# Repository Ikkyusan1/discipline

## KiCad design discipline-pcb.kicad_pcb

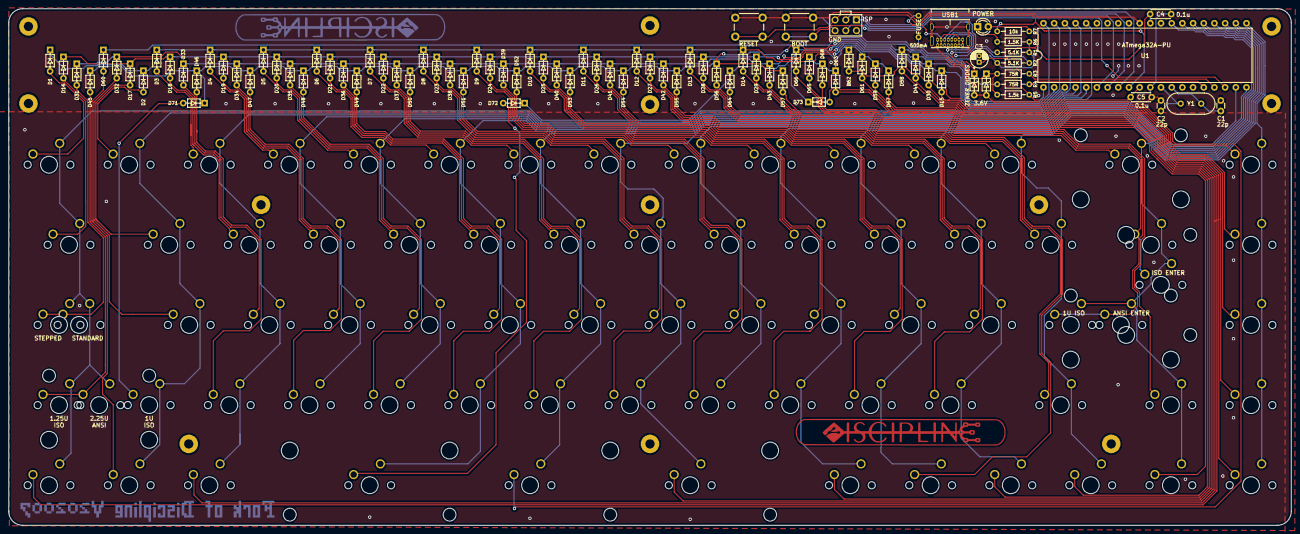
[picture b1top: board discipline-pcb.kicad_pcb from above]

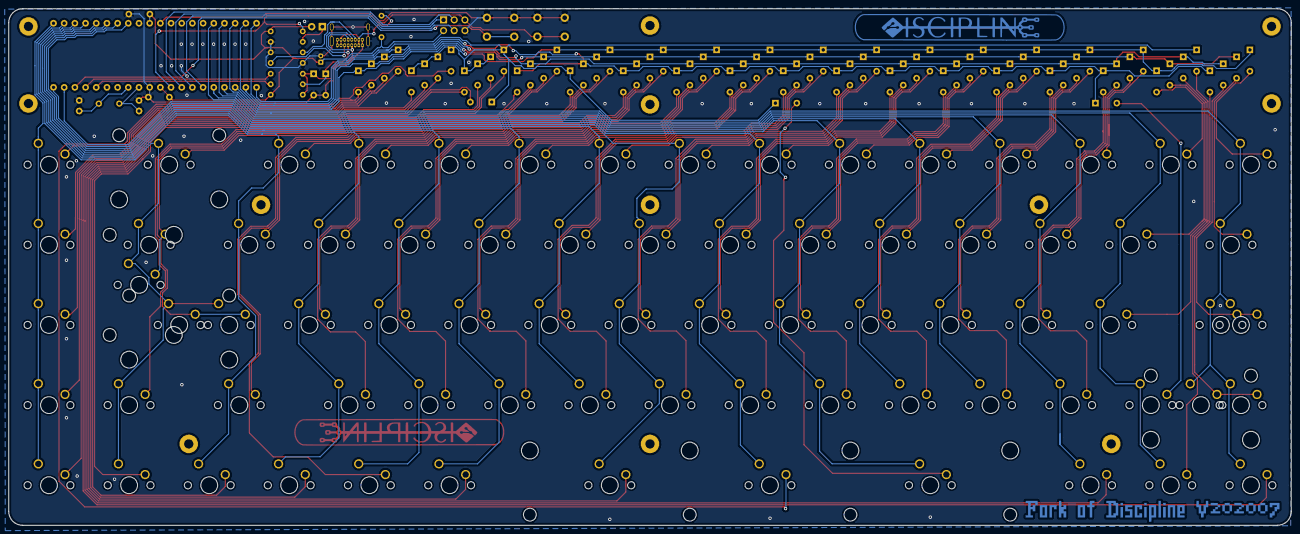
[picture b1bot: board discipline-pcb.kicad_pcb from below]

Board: 2 copper layers, 304.9 x 122.8 mm, 174 parts (4 on the bottom side), 108 nets.

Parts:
BOOT1: BOOT; SW_PUSH_6mm
C1, C2: 22p; C_Disc_D3.0mm_W1.6mm_P2.50mm
C3: 4.7u; CP_Radial_D4.0mm_P1.50mm
C4, C5: 0.1u; C_Disc_D4.3mm_W1.9mm_P5.00mm
D1, D2, D3, D4, D5, D6, D7, D8, D9, D10, D11, D12, D13, D14, D15, D16, D17, D18, D19, D20, D21, D22, D23, D24, D25, D26, D27, D28, D29, D30, D31, D32, D33, D34, D35, D36, D37, D38, D39, D40, D41, D42, D43, D44, D45, D46, D47, D48, D49, D50, D51, D52, D53, D54, D55, D56, D57, D58, D59, D60, D61, D62, D63, D64, D65, D66, D67, D68, D71, D72, D73: D_DO-35_SOD27_P5.08mm_Horizontal
D69, D70: 3.6V; D_DO-35_SOD27_P5.08mm_Horizontal
F1: 500mA; polyfuse_5.1mm
J1: AVR-ISP-6; AVR_ICSP_3x2
LED1: POWER; LED_D3.0mm
R1, R2: 5.1k; R_Axial_DIN0204_L3.6mm_D1.6mm_P7.62mm_Horizontal
R3, R4: 75R; R_Axial_DIN0204_L3.6mm_D1.6mm_P7.62mm_Horizontal
R5: 1.5k; R_Axial_DIN0204_L3.6mm_D1.6mm_P7.62mm_Horizontal
R6: 1.5K; R_Axial_DIN0204_L3.6mm_D1.6mm_P7.62mm_Horizontal
R7: 10k; R_Axial_DIN0204_L3.6mm_D1.6mm_P7.62mm_Horizontal
RESET1: RESET; SW_PUSH_6mm
Ref**: Val**; logo_mask
Ref**#2, Ref**#3: Val**; logo
Ref**#4: Val**; logo_mask
Ref**#5: Val**; version_mask
Ref**#6: Val**; version
SW1, SW2, SW3, SW4, SW5, SW6, SW7, SW8, SW9, SW10, SW11, SW12, SW13, SW15, SW17, SW18, SW19, SW20, SW21, SW22, SW23, SW24, SW25, SW26, SW27, SW28, SW30, SW32, SW33, SW34, SW35, SW36, SW37, SW38, SW39, SW40, SW41, SW42, SW44, SW46, SW47, SW48, SW49, SW50, SW51, SW52, SW53, SW54, SW55, SW57, SW58, SW59, SW60, SW61, SW62, SW64, SW65, SW66, SW67, SW68, SW75, SW77: KEYSW; SW_Cherry_MX1A_1.00u_PCB-NOSCREEN
SW14: KEYSW; SW_Cherry_MX1A_2.00u_PCBNOSCREEN
SW16, SW29: KEYSW; SW_Cherry_MX1A_1.50u_PCBNOSCREEN
SW31, SW56: KEYSW; SW_Cherry_MX1A_1.75u_PCBNOSCREEN
SW43, SW45: KEYSW; SW_Cherry_MX1A_2.25u_PCBNOSCREEN
SW63, SW69, SW78: KEYSW; SW_Cherry_MX1A_1.25u_PCBNOSCREEN
SW76: KEYSW; SW_Cherry_MX1A_ISOEnter_PCB_ReversedStabilizer
SW80, SW81: KEYSW; SW_Cherry_MX1A_3.00u_PCBNOSCREEN
U1: ATmega32A-PU; DIP-40_W15.24mm
USB1: USB_C_GCT_USB4085
Y1: Crystal; Crystal_HC49-4H_Vertical

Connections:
+5V: C3.1, C4.1, C5.1, F1.1, J1.2, LED1.2, R5.1, R7.1, U1.10, U1.30
D+: R4.1, U1.16
D-: R3.1, U1.17
GND: BOOT1.1, C1.2, C2.2, C3.2, C4.2, C5.2, D69.2, D70.2, J1.6, R1.1, R2.2, R6.2, RESET1.1, U1.11, U1.31, USB1.A1, USB1.A12, USB1.B1, USB1.B12, USB1.S1
MISO: J1.1, U1.7
MOSI: J1.4, U1.6
unnamed: C1.1, U1.13, Y1.1
unnamed: C2.1, U1.12, Y1.2
unnamed: D1.2, SW1.2
unnamed: D2.2, SW2.2
unnamed: D3.2, SW3.2
unnamed: D4.2, SW4.2
unnamed: D5.2, SW5.2
unnamed: D6.2, SW6.2
unnamed: D7.2, SW7.2
unnamed: D8.2, SW8.2
unnamed: D9.2, SW9.2
unnamed: D10.2, SW10.2
unnamed: D11.2, SW11.2
unnamed: D12.2, SW12.2
unnamed: D13.2, SW13.2
unnamed: D14.2, SW14.2
unnamed: D15.2, SW15.2
unnamed: D16.2, SW16.2
unnamed: D17.2, SW17.2
unnamed: D18.2, SW18.2
unnamed: D19.2, SW19.2
unnamed: D20.2, SW20.2
unnamed: D21.2, SW21.2
unnamed: D22.2, SW22.2
unnamed: D23.2, SW23.2
unnamed: D24.2, SW24.2
unnamed: D25.2, SW25.2
unnamed: D26.2, SW26.2
unnamed: D27.2, SW27.2
unnamed: D28.2, SW28.2
unnamed: D29.2, SW29.2, SW76.2
unnamed: D30.2, SW30.2
unnamed: D31.2, SW31.2, SW69.2
unnamed: D32.2, SW32.2
unnamed: D33.2, SW33.2
unnamed: D34.2, SW34.2
unnamed: D35.2, SW35.2
unnamed: D36.2, SW36.2
unnamed: D37.2, SW37.2
unnamed: D38.2, SW38.2
unnamed: D39.2, SW39.2
unnamed: D40.2, SW40.2
unnamed: D41.2, SW41.2
unnamed: D42.2, SW42.2
unnamed: D43.2, SW43.2, SW77.2
unnamed: D44.2, SW44.2
unnamed: D45.2, SW45.2, SW78.2
unnamed: D46.2, SW46.2
unnamed: D47.2, SW47.2
unnamed: D48.2, SW48.2
unnamed: D49.2, SW49.2
unnamed: D50.2, SW50.2
unnamed: D51.2, SW51.2
unnamed: D52.2, SW52.2
unnamed: D53.2, SW53.2
unnamed: D54.2, SW54.2
unnamed: D55.2, SW55.2
unnamed: D56.2, SW56.2
unnamed: D57.2, SW57.2
unnamed: D58.2, SW58.2
unnamed: D59.2, SW59.2
unnamed: D60.2, SW60.2
unnamed: D61.2, SW61.2
unnamed: D62.2, SW62.2
unnamed: D63.2, SW63.2
unnamed: D64.2, SW64.2
unnamed: D65.2, SW65.2
unnamed: D66.2, SW66.2
unnamed: D67.2, SW67.2
unnamed: D68.2, SW68.2
unnamed: D69.1, R3.2, R5.2, USB1.A7, USB1.B7
unnamed: D70.1, R4.2, USB1.A6, USB1.B6
unnamed: D71.2, SW75.2
unnamed: D72.2, SW80.2
unnamed: D73.2, SW81.2
unnamed: LED1.1, R6.1
unnamed: R1.2, USB1.A5
unnamed: R2.1, USB1.B5
SCK: J1.3, U1.8
VCC: F1.2, USB1.A4, USB1.A9, USB1.B4, USB1.B9
boot: BOOT1.2, U1.18
col0: SW1.1, SW16.1, SW31.1, SW45.1, SW59.1, SW69.1, SW78.1, U1.38
col1: SW2.1, SW17.1, SW32.1, SW60.1, SW75.1, U1.4
col2: SW3.1, SW18.1, SW33.1, SW46.1, SW61.1, U1.37
col3: SW4.1, SW19.1, SW34.1, SW47.1, U1.5
col4: SW5.1, SW20.1, SW35.1, SW48.1, U1.36
col5: SW6.1, SW21.1, SW36.1, SW49.1, SW80.1, U1.19
col6: SW7.1, SW22.1, SW37.1, SW50.1, SW62.1, U1.20
col7: SW8.1, SW23.1, SW38.1, SW51.1, SW81.1, U1.28
col8: SW9.1, SW24.1, SW39.1, SW52.1, U1.27
col9: SW10.1, SW25.1, SW40.1, SW53.1, SW63.1, U1.26
col10: SW11.1, SW26.1, SW41.1, SW54.1, SW64.1, U1.25
col11: SW12.1, SW27.1, SW42.1, SW55.1, SW68.1, U1.24
col12: SW13.1, SW28.1, SW56.1, SW65.1, U1.23
col13: SW14.1, SW29.1, SW43.1, SW57.1, SW66.1, SW76.1, SW77.1, U1.22
col14: SW15.1, SW30.1, SW44.1, SW58.1, SW67.1, U1.21
reset: J1.5, R7.2, RESET1.2, U1.9
row0: D1.1, D2.1, D3.1, D4.1, D5.1, D6.1, D7.1, D8.1, D9.1, D10.1, D11.1, D12.1, D13.1, D14.1, D15.1, U1.3
row1: D16.1, D17.1, D18.1, D19.1, D20.1, D21.1, D22.1, D23.1, D24.1, D25.1, D26.1, D27.1, D28.1, D29.1, D30.1, U1.39
row2: D31.1, D32.1, D33.1, D34.1, D35.1, D36.1, D37.1, D38.1, D39.1, D40.1, D41.1, D42.1, D43.1, D44.1, U1.2
row3: D45.1, D46.1, D47.1, D48.1, D49.1, D50.1, D51.1, D52.1, D53.1, D54.1, D55.1, D56.1, D57.1, D58.1, D71.1, U1.40
row4: D59.1, D60.1, D61.1, D62.1, D63.1, D64.1, D65.1, D66.1, D67.1, D68.1, D72.1, D73.1, U1.1

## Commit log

2020-06-30 Learning stuff
    WIP for an attempt to create an ISO layout + split spacebar + middle
    button
2020-07-09 "Split spacebar + middle button" design completed
    Re-integrated ANSI/ISO layout from coseyfannitutti v2, made some
    corrections, added logo...
    PCB proto is ordered, let's see how it turns out.
